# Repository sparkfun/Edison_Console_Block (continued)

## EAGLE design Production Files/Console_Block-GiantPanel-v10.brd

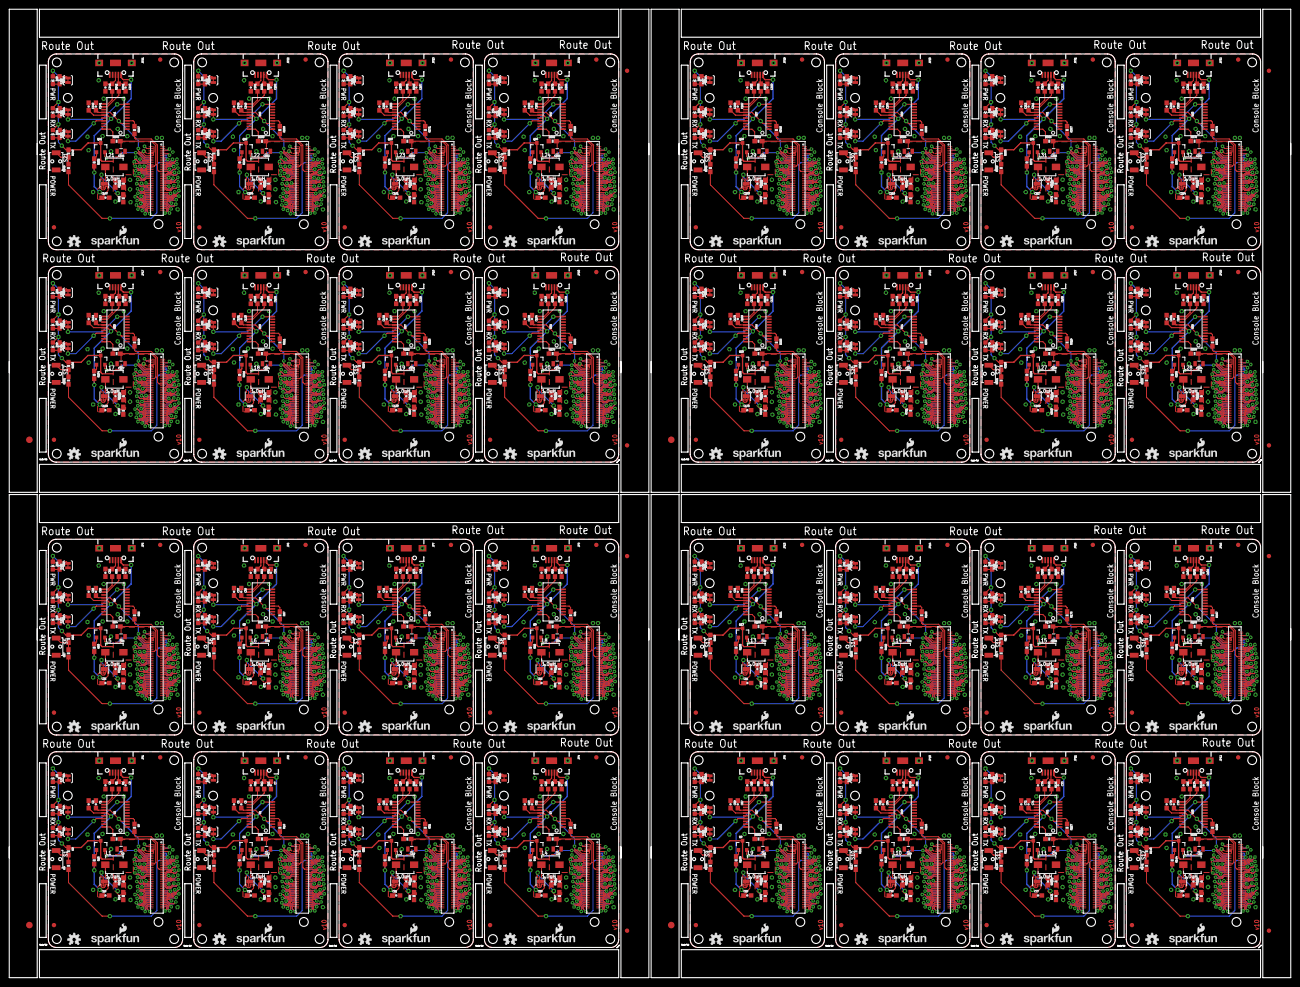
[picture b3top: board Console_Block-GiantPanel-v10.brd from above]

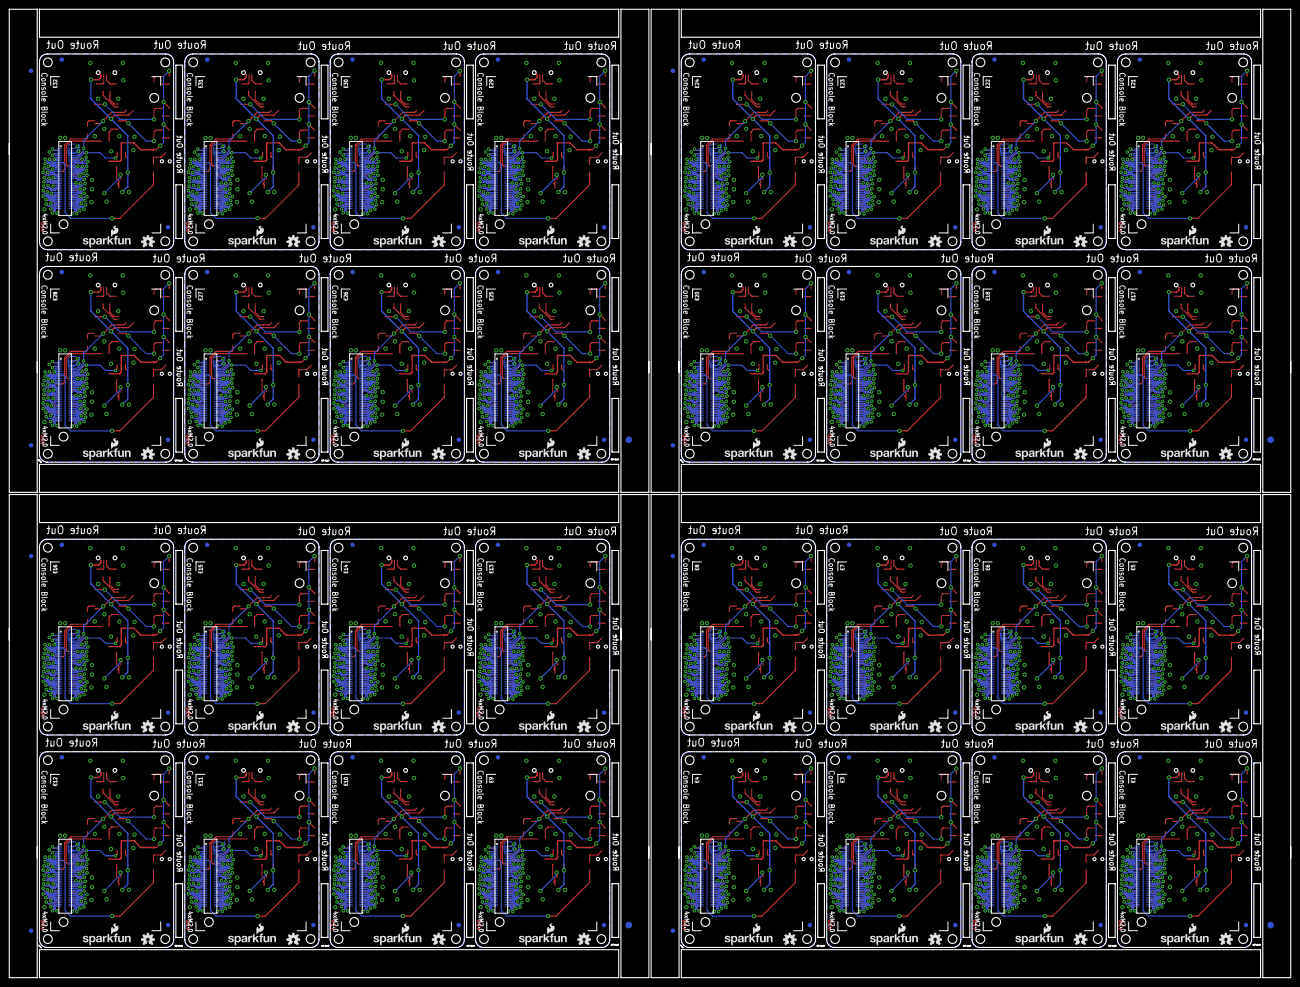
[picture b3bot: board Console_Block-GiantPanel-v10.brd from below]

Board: 2 copper layers, 291.1 x 220.0 mm, 1336 parts (204 on the bottom side), 2464 nets.

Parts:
C1, C2, C5, C6, C15, C16, C22, C23, C29, C30, C36, C37, C43, C44, C50, C51, C57, C58, C64, C65, C71, C72, C78, C79, C85, C86, C92, C93, C99, C100, C106, C107, C113, C114, C120, C121, C127, C128, C134, C135, C141, C142, C148, C149, C155, C156, C162, C163, C169, C170, C176, C177, C183, C184, C190, C191, C197, C198, C204, C205, C211, C212, C218, C219: 0.1uF; 0603-CAP
C3, C4, C7, C9, C11, C13, C17, C18, C20, C24, C25, C27, C31, C32, C34, C38, C39, C41, C45, C46, C48, C52, C53, C55, C59, C60, C62, C66, C67, C69, C73, C74, C76, C80, C81, C83, C87, C88, C90, C94, C95, C97, C101, C102, C104, C108, C109, C111, C115, C116, C118, C122, C123, C125, C129, C130, C132, C136, C137, C139, C143, C144, C146, C150, C151, C153, C157, C158, C160, C164, C165, C167, C171, C172, C174, C178, C179, C181, C185, C186, C188, C192, C193, C195, C199, C200, C202, C206, C207, C209, C213, C214, C216, C220, C221, C223: 47pF; 0603-CAP
C8, C12, C19, C26, C33, C40, C47, C54, C61, C68, C75, C82, C89, C96, C103, C110, C117, C124, C131, C138, C145, C152, C159, C166, C173, C180, C187, C194, C201, C208, C215, C222: 22uF; 0805
C10, C14, C21, C28, C35, C42, C49, C56, C63, C70, C77, C84, C91, C98, C105, C112, C119, C126, C133, C140, C147, C154, C161, C168, C175, C182, C189, C196, C203, C210, C217, C224: 4.7uF; 0603-CAP
D1, D4, D7, D10, D13, D16, D19, D22, D25, D28, D31, D34, D37, D40, D43, D46, D49, D52, D55, D58, D61, D64, D67, D70, D73, D76, D79, D82, D85, D88, D91, D94: RED; LED-0603
D2, D5, D8, D11, D14, D17, D20, D23, D26, D29, D32, D35, D38, D41, D44, D47, D50, D53, D56, D59, D62, D65, D68, D71, D74, D77, D80, D83, D86, D89, D92, D95: YELLOW; LED-0603
D3, D6, D9, D12, D15, D18, D21, D24, D27, D30, D33, D36, D39, D42, D45, D48, D51, D54, D57, D60, D63, D66, D69, D72, D75, D78, D81, D84, D87, D90, D93, D96: BLUE; LED-0603
E1, E2, E3, E4, E5, E6, E7, E8, E9, E10, E11, E12, E13, E14, E15, E16, E17, E18, E19, E20, E21, E22, E23, E24, E25, E26, E27, E28, E29, E30, E31, E32: EDISON_CONNECTOR_FULLMOUNTING_HOLES; EDISON_DAUGHTER
E$1, E$2, E$9, E$10, E$15, E$16, E$21, E$22: FIDUCIAL-1.5X3
E$3, E$4, E$5, E$6, E$7, E$8, E$11, E$12, E$13, E$14, E$17, E$18, E$19, E$20, E$23, E$24: FIDUCIAL-1X2
FID1, FID2, FID3, FID4, FID5, FID6, FID7, FID8, FID9, FID10, FID11, FID12, FID13, FID14, FID15, FID16, FID17, FID18, FID19, FID20, FID21, FID22, FID23, FID24, FID25, FID26, FID27, FID28, FID29, FID30, FID31, FID32, FID33, FID34, FID35, FID36, FID37, FID38, FID39, FID40, FID41, FID42, FID43, FID44, FID45, FID46, FID47, FID48, FID49, FID50, FID51, FID52, FID53, FID54, FID55, FID56, FID57, FID58, FID59, FID60, FID61, FID62, FID63, FID64, FID65, FID66, FID67, FID68, FID69, FID70, FID71, FID72, FID73, FID74, FID75, FID76, FID77, FID78, FID79, FID80, FID81, FID82, FID83, FID84, FID85, FID86, FID87, FID88, FID89, FID90, FID91, FID92, FID93, FID94, FID95, FID96, FID97, FID98, FID99, FID100, FID101, FID102, FID103, FID104, FID105, FID106, FID107, FID108, FID109, FID110, FID111, FID112, FID113, FID114, FID115, FID116, FID117, FID118, FID119, FID120, FID121, FID122, FID123, FID124, FID125, FID126, FID127, FID128: FIDUCIAL1X2; FIDUCIAL-1X2
JP1, JP2, JP3, JP4, JP5, JP6, JP7, JP8, JP9, JP10, JP11, JP12, JP13, JP14, JP15, JP16, JP17, JP18, JP19, JP20, JP21, JP22, JP23, JP24, JP25, JP26, JP27, JP28, JP29, JP30, JP31, JP32: USB_MICROB; USB-B-MICRO-SMD_V03
L1, L2, L3, L4, L5, L6, L7, L8, L9, L10, L11, L12, L13, L14, L15, L16, L17, L18, L19, L20, L21, L22, L23, L24, L25, L26, L27, L28, L29, L30, L31, L32: 1.0uH; INDUCTOR-SRP4020
LOGO1, LOGO3, LOGO6, LOGO7, LOGO10, LOGO11, LOGO14, LOGO15, LOGO18, LOGO19, LOGO22, LOGO23, LOGO26, LOGO27, LOGO30, LOGO31, LOGO34, LOGO35, LOGO38, LOGO39, LOGO42, LOGO43, LOGO46, LOGO47, LOGO50, LOGO51, LOGO54, LOGO55, LOGO58, LOGO59, LOGO62, LOGO63, LOGO66, LOGO67, LOGO70, LOGO71, LOGO74, LOGO75, LOGO78, LOGO79, LOGO82, LOGO83, LOGO86, LOGO87, LOGO90, LOGO91, LOGO94, LOGO95, LOGO98, LOGO99, LOGO102, LOGO103, LOGO106, LOGO107, LOGO110, LOGO111, LOGO114, LOGO115, LOGO118, LOGO119, LOGO122, LOGO123, LOGO126, LOGO127: SFE_LOGO_NAME_FLAME.1_INCH; SFE_LOGO_NAME_FLAME_.1
LOGO2, LOGO4, LOGO5, LOGO8, LOGO9, LOGO12, LOGO13, LOGO16, LOGO17, LOGO20, LOGO21, LOGO24, LOGO25, LOGO28, LOGO29, LOGO32, LOGO33, LOGO36, LOGO37, LOGO40, LOGO41, LOGO44, LOGO45, LOGO48, LOGO49, LOGO52, LOGO53, LOGO56, LOGO57, LOGO60, LOGO61, LOGO64, LOGO65, LOGO68, LOGO69, LOGO72, LOGO73, LOGO76, LOGO77, LOGO80, LOGO81, LOGO84, LOGO85, LOGO88, LOGO89, LOGO92, LOGO93, LOGO96, LOGO97, LOGO100, LOGO101, LOGO104, LOGO105, LOGO108, LOGO109, LOGO112, LOGO113, LOGO116, LOGO117, LOGO120, LOGO121, LOGO124, LOGO125, LOGO128: OSHW-LOGOS; OSHW-LOGO-S
Q1, Q2, Q3, Q4, Q5, Q6, Q7, Q8, Q9, Q10, Q11, Q12, Q13, Q14, Q15, Q16, Q17, Q18, Q19, Q20, Q21, Q22, Q23, Q24, Q25, Q26, Q27, Q28, Q29, Q30, Q31, Q32: BSS138; SOT23-3
R1, R2, R11, R12, R25, R26, R37, R38, R49, R50, R61, R62, R73, R74, R85, R86, R97, R98, R109, R110, R121, R122, R133, R134, R145, R146, R157, R158, R169, R170, R181, R182, R193, R194, R205, R206, R217, R218, R229, R230, R241, R242, R253, R254, R265, R266, R277, R278, R289, R290, R301, R302, R313, R314, R325, R326, R337, R338, R349, R350, R361, R362, R373, R374: 27; 0603
R3, R4, R5, R10, R15, R16, R17, R24, R27, R28, R29, R36, R39, R40, R41, R48, R51, R52, R53, R60, R63, R64, R65, R72, R75, R76, R77, R84, R87, R88, R89, R96, R99, R100, R101, R108, R111, R112, R113, R120, R123, R124, R125, R132, R135, R136, R137, R144, R147, R148, R149, R156, R159, R160, R161, R168, R171, R172, R173, R180, R183, R184, R185, R192, R195, R196, R197, R204, R207, R208, R209, R216, R219, R220, R221, R228, R231, R232, R233, R240, R243, R244, R245, R252, R255, R256, R257, R264, R267, R268, R269, R276, R279, R280, R281, R288, R291, R292, R293, R300, R303, R304, R305, R312, R315, R316, R317, R324, R327, R328, R329, R336, R339, R340, R341, R348, R351, R352, R353, R360, R363, R364, R365, R372, R375, R376, R377, R384: 1K; 0603-RES
R6, R7, R18, R19, R30, R31, R42, R43, R54, R55, R66, R67, R78, R79, R90, R91, R102, R103, R114, R115, R126, R127, R138, R139, R150, R151, R162, R163, R174, R175, R186, R187, R198, R199, R210, R211, R222, R223, R234, R235, R246, R247, R258, R259, R270, R271, R282, R283, R294, R295, R306, R307, R318, R319, R330, R331, R342, R343, R354, R355, R366, R367, R378, R379: 100; 0603-RES
R8, R20, R32, R44, R56, R68, R80, R92, R104, R116, R128, R140, R152, R164, R176, R188, R200, R212, R224, R236, R248, R260, R272, R284, R296, R308, R320, R332, R344, R356, R368, R380: 10K; 0603-RES
R9, R21, R33, R45, R57, R69, R81, R93, R105, R117, R129, R141, R153, R165, R177, R189, R201, R213, R225, R237, R249, R261, R273, R285, R297, R309, R321, R333, R345, R357, R369, R381: 22; 0603-RES
R13, R22, R34, R46, R58, R70, R82, R94, R106, R118, R130, R142, R154, R166, R178, R190, R202, R214, R226, R238, R250, R262, R274, R286, R298, R310, R322, R334, R346, R358, R370, R382: 680k; 0603-RES
R14, R23, R35, R47, R59, R71, R83, R95, R107, R119, R131, R143, R155, R167, R179, R191, R203, R215, R227, R239, R251, R263, R275, R287, R299, R311, R323, R335, R347, R359, R371, R383: 120k; 0603-RES
S1, S2, S3, S4, S5, S6, S7, S8, S9, S10, S11, S12, S13, S14, S15, S16, S17, S18, S19, S20, S21, S22, S23, S24, S25, S26, S27, S28, S29, S30, S31, S32: POWER; TACTILE_SWITCH-SMD-RIGHT-ANGLE
SJ1, SJ2, SJ3, SJ4, SJ5, SJ6, SJ7, SJ8, SJ9, SJ10, SJ11, SJ12, SJ13, SJ14, SJ15, SJ16, SJ17, SJ18, SJ19, SJ20, SJ21, SJ22, SJ23, SJ24, SJ25, SJ26, SJ27, SJ28, SJ29, SJ30, SJ31, SJ32, SJ33, SJ34, SJ35, SJ36, SJ37, SJ38, SJ39, SJ40, SJ41, SJ42, SJ43, SJ44, SJ45, SJ46, SJ47, SJ48, SJ49, SJ50, SJ51, SJ52, SJ53, SJ54, SJ55, SJ56, SJ57, SJ58, SJ59, SJ60, SJ61, SJ62, SJ63, SJ64, SJ65, SJ66, SJ67, SJ68, SJ69, SJ70, SJ71, SJ72, SJ73, SJ74, SJ75, SJ76, SJ77, SJ78, SJ79, SJ80, SJ81, SJ82, SJ83, SJ84, SJ85, SJ86, SJ87, SJ88, SJ89, SJ90, SJ91, SJ92, SJ93, SJ94, SJ95, SJ96: JUMPER-PAD-2-NC_BY_TRACE; PAD-JUMPER-2-NC_BY_TRACE_YES_SILK
U1, U2, U5, U7, U9, U11, U13, U15, U17, U19, U21, U23, U25, U27, U29, U31, U33, U35, U37, U39, U41, U43, U45, U47, U49, U51, U53, U55, U57, U59, U61, U63: FT231XS-U; SSOP20_L
U3, U4, U6, U8, U10, U12, U14, U16, U18, U20, U22, U24, U26, U28, U30, U32, U34, U36, U38, U40, U42, U44, U46, U48, U50, U52, U54, U56, U58, U60, U62, U64: TPS62065; WSON-8-PAD
U$1, U$2, U$3, U$4, U$5, U$6, U$7, U$8, U$9, U$10, U$11, U$12, U$13, U$14, U$15, U$16, U$17, U$18, U$19, U$20, U$21, U$22, U$23, U$24, U$25, U$26, U$27, U$28, U$29, U$30, U$31, U$32: EDISON_CONNECTOR_FULLHEADER; DF40C-70DP-0.4(51)

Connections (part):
1.8V: C1.2, E1.12, U2.3, U2.14, U$3.12
1.8V1: C5.2, E2.12, U1.3, U1.14, U$1.12
1.8V2: C15.2, E3.12, U5.3, U5.14, U$2.12
1.8V3: C22.2, E4.12, U7.3, U7.14, U$4.12
1.8V4: C29.2, E5.12, U9.3, U9.14, U$5.12
1.8V5: C36.2, E6.12, U11.3, U11.14, U$6.12
1.8V6: C43.2, E7.12, U13.3, U13.14, U$7.12
1.8V7: C50.2, E8.12, U15.3, U15.14, U$8.12
1.8V8: C57.2, E9.12, U17.3, U17.14, U$9.12
1.8V9: C64.2, E10.12, U19.3, U19.14, U$10.12
1.8V10: C71.2, E11.12, U21.3, U21.14, U$11.12
1.8V11: C78.2, E12.12, U23.3, U23.14, U$12.12
1.8V12: C85.2, E13.12, U25.3, U25.14, U$13.12
1.8V13: C92.2, E14.12, U27.3, U27.14, U$14.12
1.8V14: C99.2, E15.12, U29.3, U29.14, U$15.12
1.8V15: C106.2, E16.12, U31.3, U31.14, U$16.12
1.8V16: C113.2, E17.12, U33.3, U33.14, U$17.12
1.8V17: C120.2, E18.12, U35.3, U35.14, U$18.12
1.8V18: C127.2, E19.12, U37.3, U37.14, U$19.12
1.8V19: C134.2, E20.12, U39.3, U39.14, U$20.12
1.8V20: C141.2, E21.12, U41.3, U41.14, U$21.12
1.8V21: C148.2, E22.12, U43.3, U43.14, U$22.12
1.8V22: C155.2, E23.12, U45.3, U45.14, U$23.12
1.8V23: C162.2, E24.12, U47.3, U47.14, U$24.12
1.8V24: C169.2, E25.12, U49.3, U49.14, U$25.12
1.8V25: C176.2, E26.12, U51.3, U51.14, U$26.12
1.8V26: C183.2, E27.12, U53.3, U53.14, U$27.12
1.8V27: C190.2, E28.12, U55.3, U55.14, U$28.12
1.8V28: C197.2, E29.12, U57.3, U57.14, U$29.12
1.8V29: C204.2, E30.12, U59.3, U59.14, U$30.12
1.8V30: C211.2, E31.12, U61.3, U61.14, U$31.12
1.8V31: C218.2, E32.12, U63.3, U63.14, U$32.12
3.3V: E1.8, E1.10, U$3.8, U$3.10
3.3V1: E2.8, E2.10, U$1.8, U$1.10
3.3V2: E3.8, E3.10, U$2.8, U$2.10
3.3V3: E4.8, E4.10, U$4.8, U$4.10
3.3V4: E5.8, E5.10, U$5.8, U$5.10
3.3V5: E6.8, E6.10, U$6.8, U$6.10
3.3V6: E7.8, E7.10, U$7.8, U$7.10
3.3V7: E8.8, E8.10, U$8.8, U$8.10
3.3V8: E9.8, E9.10, U$9.8, U$9.10
3.3V9: E10.8, E10.10, U$10.8, U$10.10
3.3V10: E11.8, E11.10, U$11.8, U$11.10
3.3V11: E12.8, E12.10, U$12.8, U$12.10
3.3V12: E13.8, E13.10, U$13.8, U$13.10
3.3V13: E14.8, E14.10, U$14.8, U$14.10
3.3V14: E15.8, E15.10, U$15.8, U$15.10
3.3V15: E16.8, E16.10, U$16.8, U$16.10
3.3V16: E17.8, E17.10, U$17.8, U$17.10
3.3V17: E18.8, E18.10, U$18.8, U$18.10
3.3V18: E19.8, E19.10, U$19.8, U$19.10
3.3V19: E20.8, E20.10, U$20.8, U$20.10
3.3V20: E21.8, E21.10, U$21.8, U$21.10
3.3V21: E22.8, E22.10, U$22.8, U$22.10
3.3V22: E23.8, E23.10, U$23.8, U$23.10
3.3V23: E24.8, E24.10, U$24.8, U$24.10
3.3V24: E25.8, E25.10, U$25.8, U$25.10
3.3V25: E26.8, E26.10, U$26.8, U$26.10
3.3V26: E27.8, E27.10, U$27.8, U$27.10
3.3V27: E28.8, E28.10, U$28.8, U$28.10
3.3V28: E29.8, E29.10, U$29.8, U$29.10
3.3V29: E30.8, E30.10, U$30.8, U$30.10
3.3V30: E31.8, E31.10, U$31.8, U$31.10
3.3V31: E32.8, E32.10, U$32.8, U$32.10
5V: C2.2, C10.1, JP1.VBUS1, R10.2, U2.15, U4.5, U4.7, U4.8
5V1: C6.2, C14.1, JP2.VBUS1, R24.2, U1.15, U3.5, U3.7, U3.8
5V2: C16.2, C21.1, JP3.VBUS1, R36.2, U5.15, U6.5, U6.7, U6.8
5V3: C23.2, C28.1, JP4.VBUS1, R48.2, U7.15, U8.5, U8.7, U8.8
5V4: C30.2, C35.1, JP5.VBUS1, R60.2, U9.15, U10.5, U10.7, U10.8
5V5: C37.2, C42.1, JP6.VBUS1, R72.2, U11.15, U12.5, U12.7, U12.8
5V6: C44.2, C49.1, JP7.VBUS1, R84.2, U13.15, U14.5, U14.7, U14.8
5V7: C51.2, C56.1, JP8.VBUS1, R96.2, U15.15, U16.5, U16.7, U16.8
5V8: C58.2, C63.1, JP9.VBUS1, R108.2, U17.15, U18.5, U18.7, U18.8
5V9: C65.2, C70.1, JP10.VBUS1, R120.2, U19.15, U20.5, U20.7, U20.8
5V10: C72.2, C77.1, JP11.VBUS1, R132.2, U21.15, U22.5, U22.7, U22.8
5V11: C79.2, C84.1, JP12.VBUS1, R144.2, U23.15, U24.5, U24.7, U24.8
5V12: C86.2, C91.1, JP13.VBUS1, R156.2, U25.15, U26.5, U26.7, U26.8
5V13: C93.2, C98.1, JP14.VBUS1, R168.2, U27.15, U28.5, U28.7, U28.8
5V14: C100.2, C105.1, JP15.VBUS1, R180.2, U29.15, U30.5, U30.7, U30.8
5V15: C107.2, C112.1, JP16.VBUS1, R192.2, U31.15, U32.5, U32.7, U32.8
5V16: C114.2, C119.1, JP17.VBUS1, R204.2, U33.15, U34.5, U34.7, U34.8
5V17: C121.2, C126.1, JP18.VBUS1, R216.2, U35.15, U36.5, U36.7, U36.8
5V18: C128.2, C133.1, JP19.VBUS1, R228.2, U37.15, U38.5, U38.7, U38.8
5V19: C135.2, C140.1, JP20.VBUS1, R240.2, U39.15, U40.5, U40.7, U40.8
5V20: C142.2, C147.1, JP21.VBUS1, R252.2, U41.15, U42.5, U42.7, U42.8
5V21: C149.2, C154.1, JP22.VBUS1, R264.2, U43.15, U44.5, U44.7, U44.8
5V22: C156.2, C161.1, JP23.VBUS1, R276.2, U45.15, U46.5, U46.7, U46.8
5V23: C163.2, C168.1, JP24.VBUS1, R288.2, U47.15, U48.5, U48.7, U48.8
5V24: C170.2, C175.1, JP25.VBUS1, R300.2, U49.15, U50.5, U50.7, U50.8
5V25: C177.2, C182.1, JP26.VBUS1, R312.2, U51.15, U52.5, U52.7, U52.8
5V26: C184.2, C189.1, JP27.VBUS1, R324.2, U53.15, U54.5, U54.7, U54.8
5V27: C191.2, C196.1, JP28.VBUS1, R336.2, U55.15, U56.5, U56.7, U56.8
5V28: C198.2, C203.1, JP29.VBUS1, R348.2, U57.15, U58.5, U58.7, U58.8
5V29: C205.2, C210.1, JP30.VBUS1, R360.2, U59.15, U60.5, U60.7, U60.8
5V30: C212.2, C217.1, JP31.VBUS1, R372.2, U61.15, U62.5, U62.7, U62.8
5V31: C219.2, C224.1, JP32.VBUS1, R384.2, U63.15, U64.5, U64.7, U64.8
DCIN: E1.14, Q1.2, U$3.14
DCIN1: E2.14, Q2.2, U$1.14
DCIN2: E3.14, Q3.2, U$2.14
DCIN3: E4.14, Q4.2, U$4.14
DCIN4: E5.14, Q5.2, U$5.14
DCIN5: E6.14, Q6.2, U$6.14
DCIN6: E7.14, Q7.2, U$7.14
DCIN7: E8.14, Q8.2, U$8.14
DCIN8: E9.14, Q9.2, U$9.14
DCIN9: E10.14, Q10.2, U$10.14
DCIN10: E11.14, Q11.2, U$11.14
DCIN11: E12.14, Q12.2, U$12.14
DCIN12: E13.14, Q13.2, U$13.14
DCIN13: E14.14, Q14.2, U$14.14
DCIN14: E15.14, Q15.2, U$15.14
DCIN15: E16.14, Q16.2, U$16.14
DCIN16: E17.14, Q17.2, U$17.14
DCIN17: E18.14, Q18.2, U$18.14
DCIN18: E19.14, Q19.2, U$19.14
DCIN19: E20.14, Q20.2, U$20.14
DCIN20: E21.14, Q21.2, U$21.14
DCIN21: E22.14, Q22.2, U$22.14
DCIN22: E23.14, Q23.2, U$23.14
DCIN23: E24.14, Q24.2, U$24.14
DCIN24: E25.14, Q25.2, U$25.14
DCIN25: E26.14, Q26.2, U$26.14
DCIN26: E27.14, Q27.2, U$27.14
DCIN27: E28.14, Q28.2, U$28.14
DCIN28: E29.14, Q29.2, U$29.14
DCIN29: E30.14, Q30.2, U$30.14
DCIN30: E31.14, Q31.2, U$31.14
DCIN31: E32.14, Q32.2, U$32.14
FAULT: E1.19, U$3.19
FAULT1: E2.19, U$1.19
FAULT2: E3.19, U$2.19
FAULT3: E4.19, U$4.19
FAULT4: E5.19, U$5.19
FAULT5: E6.19, U$6.19
FAULT6: E7.19, U$7.19
FAULT7: E8.19, U$8.19
FAULT8: E9.19, U$9.19
FAULT9: E10.19, U$10.19
FAULT10: E11.19, U$11.19
FAULT11: E12.19, U$12.19
FAULT12: E13.19, U$13.19
FAULT13: E14.19, U$14.19
FAULT14: E15.19, U$15.19
FAULT15: E16.19, U$16.19
FAULT16: E17.19, U$17.19
FAULT17: E18.19, U$18.19
FAULT18: E19.19, U$19.19
FAULT19: E20.19, U$20.19
FAULT20: E21.19, U$21.19
FAULT21: E22.19, U$22.19
FAULT22: E23.19, U$23.19
FAULT23: E24.19, U$24.19
FAULT24: E25.19, U$25.19
FAULT25: E26.19, U$26.19
FAULT26: E27.19, U$27.19
FAULT27: E28.19, U$28.19
FAULT28: E29.19, U$29.19
FAULT29: E30.19, U$30.19
FAULT30: E31.19, U$31.19
FAULT31: E32.19, U$32.19
FW_RCVR: E1.69, U$3.69
FW_RCVR1: E2.69, U$1.69
FW_RCVR2: E3.69, U$2.69
FW_RCVR3: E4.69, U$4.69
FW_RCVR4: E5.69, U$5.69
FW_RCVR5: E6.69, U$6.69
FW_RCVR6: E7.69, U$7.69
FW_RCVR7: E8.69, U$8.69
FW_RCVR8: E9.69, U$9.69
FW_RCVR9: E10.69, U$10.69
FW_RCVR10: E11.69, U$11.69
FW_RCVR11: E12.69, U$12.69
FW_RCVR12: E13.69, U$13.69
FW_RCVR13: E14.69, U$14.69
FW_RCVR14: E15.69, U$15.69
FW_RCVR15: E16.69, U$16.69
FW_RCVR16: E17.69, U$17.69
FW_RCVR17: E18.69, U$18.69
FW_RCVR18: E19.69, U$19.69
FW_RCVR19: E20.69, U$20.69
FW_RCVR20: E21.69, U$21.69
FW_RCVR21: E22.69, U$22.69
FW_RCVR22: E23.69, U$23.69
FW_RCVR23: E24.69, U$24.69
FW_RCVR24: E25.69, U$25.69
FW_RCVR25: E26.69, U$26.69
FW_RCVR26: E27.69, U$27.69
FW_RCVR27: E28.69, U$28.69
FW_RCVR28: E29.69, U$29.69
FW_RCVR29: E30.69, U$30.69
FW_RCVR30: E31.69, U$31.69
FW_RCVR31: E32.69, U$32.69
GND: C1.1, C2.1, C3.2, C4.2, C8.2, C10.2, E1.1, E1.5, E1.9, E1.11, E1.13, E1.15, JP1.GND1, JP1.SHIELD1, JP1.SHIELD2, JP1.SHIELD3, R14.1, S1.2, SJ3.1, U2.6, U2.16, U4.1, U4.3, U4.6, U4.PAD, U$3.1, U$3.5, U$3.9, U$3.11, U$3.13, U$3.15
GND1: C5.1, C6.1, C7.2, C11.2, C12.2, C14.2, E2.1, E2.5, E2.9, E2.11, E2.13, E2.15, JP2.GND1, JP2.SHIELD1, JP2.SHIELD2, JP2.SHIELD3, R23.1, S2.2, SJ6.1, U1.6, U1.16, U3.1, U3.3, U3.6, U3.PAD, U$1.1, U$1.5, U$1.9, U$1.11, U$1.13, U$1.15
GND2: C15.1, C16.1, C17.2, C18.2, C19.2, C21.2, E3.1, E3.5, E3.9, E3.11, E3.13, E3.15, JP3.GND1, JP3.SHIELD1, JP3.SHIELD2, JP3.SHIELD3, R35.1, S3.2, SJ9.1, U5.6, U5.16, U6.1, U6.3, U6.6, U6.PAD, U$2.1, U$2.5, U$2.9, U$2.11, U$2.13, U$2.15
GND3: C22.1, C23.1, C24.2, C25.2, C26.2, C28.2, E4.1, E4.5, E4.9, E4.11, E4.13, E4.15, JP4.GND1, JP4.SHIELD1, JP4.SHIELD2, JP4.SHIELD3, R47.1, S4.2, SJ12.1, U7.6, U7.16, U8.1, U8.3, U8.6, U8.PAD, U$4.1, U$4.5, U$4.9, U$4.11, U$4.13, U$4.15
GND4: C29.1, C30.1, C31.2, C32.2, C33.2, C35.2, E5.1, E5.5, E5.9, E5.11, E5.13, E5.15, JP5.GND1, JP5.SHIELD1, JP5.SHIELD2, JP5.SHIELD3, R59.1, S5.2, SJ15.1, U9.6, U9.16, U10.1, U10.3, U10.6, U10.PAD, U$5.1, U$5.5, U$5.9, U$5.11, U$5.13, U$5.15
GND5: C36.1, C37.1, C38.2, C39.2, C40.2, C42.2, E6.1, E6.5, E6.9, E6.11, E6.13, E6.15, JP6.GND1, JP6.SHIELD1, JP6.SHIELD2, JP6.SHIELD3, R71.1, S6.2, SJ18.1, U11.6, U11.16, U12.1, U12.3, U12.6, U12.PAD, U$6.1, U$6.5, U$6.9, U$6.11, U$6.13, U$6.15
GND6: C43.1, C44.1, C45.2, C46.2, C47.2, C49.2, E7.1, E7.5, E7.9, E7.11, E7.13, E7.15, JP7.GND1, JP7.SHIELD1, JP7.SHIELD2, JP7.SHIELD3, R83.1, S7.2, SJ21.1, U13.6, U13.16, U14.1, U14.3, U14.6, U14.PAD, U$7.1, U$7.5, U$7.9, U$7.11, U$7.13, U$7.15
GND7: C50.1, C51.1, C52.2, C53.2, C54.2, C56.2, E8.1, E8.5, E8.9, E8.11, E8.13, E8.15, JP8.GND1, JP8.SHIELD1, JP8.SHIELD2, JP8.SHIELD3, R95.1, S8.2, SJ24.1, U15.6, U15.16, U16.1, U16.3, U16.6, U16.PAD, U$8.1, U$8.5, U$8.9, U$8.11, U$8.13, U$8.15
GND8: C57.1, C58.1, C59.2, C60.2, C61.2, C63.2, E9.1, E9.5, E9.9, E9.11, E9.13, E9.15, JP9.GND1, JP9.SHIELD1, JP9.SHIELD2, JP9.SHIELD3, R107.1, S9.2, SJ27.1, U17.6, U17.16, U18.1, U18.3, U18.6, U18.PAD, U$9.1, U$9.5, U$9.9, U$9.11, U$9.13, U$9.15
GND9: C64.1, C65.1, C66.2, C67.2, C68.2, C70.2, E10.1, E10.5, E10.9, E10.11, E10.13, E10.15, JP10.GND1, JP10.SHIELD1, JP10.SHIELD2, JP10.SHIELD3, R119.1, S10.2, SJ30.1, U19.6, U19.16, U20.1, U20.3, U20.6, U20.PAD, U$10.1, U$10.5, U$10.9, U$10.11, U$10.13, U$10.15
GND10: C71.1, C72.1, C73.2, C74.2, C75.2, C77.2, E11.1, E11.5, E11.9, E11.11, E11.13, E11.15, JP11.GND1, JP11.SHIELD1, JP11.SHIELD2, JP11.SHIELD3, R131.1, S11.2, SJ33.1, U21.6, U21.16, U22.1, U22.3, U22.6, U22.PAD, U$11.1, U$11.5, U$11.9, U$11.11, U$11.13, U$11.15
GND11: C78.1, C79.1, C80.2, C81.2, C82.2, C84.2, E12.1, E12.5, E12.9, E12.11, E12.13, E12.15, JP12.GND1, JP12.SHIELD1, JP12.SHIELD2, JP12.SHIELD3, R143.1, S12.2, SJ36.1, U23.6, U23.16, U24.1, U24.3, U24.6, U24.PAD, U$12.1, U$12.5, U$12.9, U$12.11, U$12.13, U$12.15
GND12: C85.1, C86.1, C87.2, C88.2, C89.2, C91.2, E13.1, E13.5, E13.9, E13.11, E13.13, E13.15, JP13.GND1, JP13.SHIELD1, JP13.SHIELD2, JP13.SHIELD3, R155.1, S13.2, SJ39.1, U25.6, U25.16, U26.1, U26.3, U26.6, U26.PAD, U$13.1, U$13.5, U$13.9, U$13.11, U$13.13, U$13.15
GND13: C92.1, C93.1, C94.2, C95.2, C96.2, C98.2, E14.1, E14.5, E14.9, E14.11, E14.13, E14.15, JP14.GND1, JP14.SHIELD1, JP14.SHIELD2, JP14.SHIELD3, R167.1, S14.2, SJ42.1, U27.6, U27.16, U28.1, U28.3, U28.6, U28.PAD, U$14.1, U$14.5, U$14.9, U$14.11, U$14.13, U$14.15
GND14: C99.1, C100.1, C101.2, C102.2, C103.2, C105.2, E15.1, E15.5, E15.9, E15.11, E15.13, E15.15, JP15.GND1, JP15.SHIELD1, JP15.SHIELD2, JP15.SHIELD3, R179.1, S15.2, SJ45.1, U29.6, U29.16, U30.1, U30.3, U30.6, U30.PAD, U$15.1, U$15.5, U$15.9, U$15.11, U$15.13, U$15.15
GND15: C106.1, C107.1, C108.2, C109.2, C110.2, C112.2, E16.1, E16.5, E16.9, E16.11, E16.13, E16.15, JP16.GND1, JP16.SHIELD1, JP16.SHIELD2, JP16.SHIELD3, R191.1, S16.2, SJ48.1, U31.6, U31.16, U32.1, U32.3, U32.6, U32.PAD, U$16.1, U$16.5, U$16.9, U$16.11, U$16.13, U$16.15
GND16: C113.1, C114.1, C115.2, C116.2, C117.2, C119.2, E17.1, E17.5, E17.9, E17.11, E17.13, E17.15, JP17.GND1, JP17.SHIELD1, JP17.SHIELD2, JP17.SHIELD3, R203.1, S17.2, SJ51.1, U33.6, U33.16, U34.1, U34.3, U34.6, U34.PAD, U$17.1, U$17.5, U$17.9, U$17.11, U$17.13, U$17.15
GND17: C120.1, C121.1, C122.2, C123.2, C124.2, C126.2, E18.1, E18.5, E18.9, E18.11, E18.13, E18.15, JP18.GND1, JP18.SHIELD1, JP18.SHIELD2, JP18.SHIELD3, R215.1, S18.2, SJ54.1, U35.6, U35.16, U36.1, U36.3, U36.6, U36.PAD, U$18.1, U$18.5, U$18.9, U$18.11, U$18.13, U$18.15
GND18: C127.1, C128.1, C129.2, C130.2, C131.2, C133.2, E19.1, E19.5, E19.9, E19.11, E19.13, E19.15, JP19.GND1, JP19.SHIELD1, JP19.SHIELD2, JP19.SHIELD3, R227.1, S19.2, SJ57.1, U37.6, U37.16, U38.1, U38.3, U38.6, U38.PAD, U$19.1, U$19.5, U$19.9, U$19.11, U$19.13, U$19.15
GND19: C134.1, C135.1, C136.2, C137.2, C138.2, C140.2, E20.1, E20.5, E20.9, E20.11, E20.13, E20.15, JP20.GND1, JP20.SHIELD1, JP20.SHIELD2, JP20.SHIELD3, R239.1, S20.2, SJ60.1, U39.6, U39.16, U40.1, U40.3, U40.6, U40.PAD, U$20.1, U$20.5, U$20.9, U$20.11, U$20.13, U$20.15
GND20: C141.1, C142.1, C143.2, C144.2, C145.2, C147.2, E21.1, E21.5, E21.9, E21.11, E21.13, E21.15, JP21.GND1, JP21.SHIELD1, JP21.SHIELD2, JP21.SHIELD3, R251.1, S21.2, SJ63.1, U41.6, U41.16, U42.1, U42.3, U42.6, U42.PAD, U$21.1, U$21.5, U$21.9, U$21.11, U$21.13, U$21.15
GND21: C148.1, C149.1, C150.2, C151.2, C152.2, C154.2, E22.1, E22.5, E22.9, E22.11, E22.13, E22.15, JP22.GND1, JP22.SHIELD1, JP22.SHIELD2, JP22.SHIELD3, R263.1, S22.2, SJ66.1, U43.6, U43.16, U44.1, U44.3, U44.6, U44.PAD, U$22.1, U$22.5, U$22.9, U$22.11, U$22.13, U$22.15
GND22: C155.1, C156.1, C157.2, C158.2, C159.2, C161.2, E23.1, E23.5, E23.9, E23.11, E23.13, E23.15, JP23.GND1, JP23.SHIELD1, JP23.SHIELD2, JP23.SHIELD3, R275.1, S23.2, SJ69.1, U45.6, U45.16, U46.1, U46.3, U46.6, U46.PAD, U$23.1, U$23.5, U$23.9, U$23.11, U$23.13, U$23.15
GND23: C162.1, C163.1, C164.2, C165.2, C166.2, C168.2, E24.1, E24.5, E24.9, E24.11, E24.13, E24.15, JP24.GND1, JP24.SHIELD1, JP24.SHIELD2, JP24.SHIELD3, R287.1, S24.2, SJ72.1, U47.6, U47.16, U48.1, U48.3, U48.6, U48.PAD, U$24.1, U$24.5, U$24.9, U$24.11, U$24.13, U$24.15
GND24: C169.1, C170.1, C171.2, C172.2, C173.2, C175.2, E25.1, E25.5, E25.9, E25.11, E25.13, E25.15, JP25.GND1, JP25.SHIELD1, JP25.SHIELD2, JP25.SHIELD3, R299.1, S25.2, SJ75.1, U49.6, U49.16, U50.1, U50.3, U50.6, U50.PAD, U$25.1, U$25.5, U$25.9, U$25.11, U$25.13, U$25.15
GND25: C176.1, C177.1, C178.2, C179.2, C180.2, C182.2, E26.1, E26.5, E26.9, E26.11, E26.13, E26.15, JP26.GND1, JP26.SHIELD1, JP26.SHIELD2, JP26.SHIELD3, R311.1, S26.2, SJ78.1, U51.6, U51.16, U52.1, U52.3, U52.6, U52.PAD, U$26.1, U$26.5, U$26.9, U$26.11, U$26.13, U$26.15
GND26: C183.1, C184.1, C185.2, C186.2, C187.2, C189.2, E27.1, E27.5, E27.9, E27.11, E27.13, E27.15, JP27.GND1, JP27.SHIELD1, JP27.SHIELD2, JP27.SHIELD3, R323.1, S27.2, SJ81.1, U53.6, U53.16, U54.1, U54.3, U54.6, U54.PAD, U$27.1, U$27.5, U$27.9, U$27.11, U$27.13, U$27.15
GND27: C190.1, C191.1, C192.2, C193.2, C194.2, C196.2, E28.1, E28.5, E28.9, E28.11, E28.13, E28.15, JP28.GND1, JP28.SHIELD1, JP28.SHIELD2, JP28.SHIELD3, R335.1, S28.2, SJ84.1, U55.6, U55.16, U56.1, U56.3, U56.6, U56.PAD, U$28.1, U$28.5, U$28.9, U$28.11, U$28.13, U$28.15
GND28: C197.1, C198.1, C199.2, C200.2, C201.2, C203.2, E29.1, E29.5, E29.9, E29.11, E29.13, E29.15, JP29.GND1, JP29.SHIELD1, JP29.SHIELD2, JP29.SHIELD3, R347.1, S29.2, SJ87.1, U57.6, U57.16, U58.1, U58.3, U58.6, U58.PAD, U$29.1, U$29.5, U$29.9, U$29.11, U$29.13, U$29.15
GND29: C204.1, C205.1, C206.2, C207.2, C208.2, C210.2, E30.1, E30.5, E30.9, E30.11, E30.13, E30.15, JP30.GND1, JP30.SHIELD1, JP30.SHIELD2, JP30.SHIELD3, R359.1, S30.2, SJ90.1, U59.6, U59.16, U60.1, U60.3, U60.6, U60.PAD, U$30.1, U$30.5, U$30.9, U$30.11, U$30.13, U$30.15
GND30: C211.1, C212.1, C213.2, C214.2, C215.2, C217.2, E31.1, E31.5, E31.9, E31.11, E31.13, E31.15, JP31.GND1, JP31.SHIELD1, JP31.SHIELD2, JP31.SHIELD3, R371.1, S31.2, SJ93.1, U61.6, U61.16, U62.1, U62.3, U62.6, U62.PAD, U$31.1, U$31.5, U$31.9, U$31.11, U$31.13, U$31.15
GND31: C218.1, C219.1, C220.2, C221.2, C222.2, C224.2, E32.1, E32.5, E32.9, E32.11, E32.13, E32.15, JP32.GND1, JP32.SHIELD1, JP32.SHIELD2, JP32.SHIELD3, R383.1, S32.2, SJ96.1, U63.6, U63.16, U64.1, U64.3, U64.6, U64.PAD, U$32.1, U$32.5, U$32.9, U$32.11, U$32.13, U$32.15
GP1: E2.48, U$1.48
GP2: E2.42, U$1.42
GP3: E2.34, U$1.34
GP4: E2.32, U$1.32
GP5: E2.30, U$1.30
GP6: E2.28, U$1.28
GP7: E2.26, U$1.26
GP8: E2.25, U$1.25
GP9: E2.24, U$1.24
GP10: E3.48, U$2.48
GP11: E3.42, U$2.42
GP12: E3.34, U$2.34
GP12_PWM0: E1.35, U$3.35
GP12_PWM1: E2.35, U$1.35
GP12_PWM2: E3.35, U$2.35
GP12_PWM3: E4.35, U$4.35
GP12_PWM4: E5.35, U$5.35
GP12_PWM5: E6.35, U$6.35
GP12_PWM6: E7.35, U$7.35
GP12_PWM7: E8.35, U$8.35
GP12_PWM8: E9.35, U$9.35
GP12_PWM9: E10.35, U$10.35
GP12_PWM10: E11.35, U$11.35
GP12_PWM11: E12.35, U$12.35
GP12_PWM12: E13.35, U$13.35
GP12_PWM13: E14.35, U$14.35
GP12_PWM14: E15.35, U$15.35
GP12_PWM15: E16.35, U$16.35
GP12_PWM16: E17.35, U$17.35
GP12_PWM17: E18.35, U$18.35
GP12_PWM18: E19.35, U$19.35
GP12_PWM19: E20.35, U$20.35
GP12_PWM20: E21.35, U$21.35
GP12_PWM21: E22.35, U$22.35
GP12_PWM22: E23.35, U$23.35
GP12_PWM23: E24.35, U$24.35
GP12_PWM24: E25.35, U$25.35
GP12_PWM25: E26.35, U$26.35
GP12_PWM26: E27.35, U$27.35
GP12_PWM27: E28.35, U$28.35
GP12_PWM28: E29.35, U$29.35
GP12_PWM29: E30.35, U$30.35
GP12_PWM30: E31.35, U$31.35
GP12_PWM31: E32.35, U$32.35
GP13: E3.32, U$2.32
GP13_PWM1: E1.33, U$3.33
GP13_PWM2: E2.33, U$1.33
GP13_PWM3: E3.33, U$2.33
GP13_PWM4: E4.33, U$4.33
GP13_PWM5: E5.33, U$5.33
GP13_PWM6: E6.33, U$6.33
GP13_PWM7: E7.33, U$7.33
GP13_PWM8: E8.33, U$8.33
GP13_PWM9: E9.33, U$9.33
GP13_PWM10: E10.33, U$10.33
GP13_PWM11: E11.33, U$11.33
GP13_PWM12: E12.33, U$12.33
GP13_PWM13: E13.33, U$13.33
GP13_PWM14: E14.33, U$14.33
GP13_PWM15: E15.33, U$15.33
GP13_PWM16: E16.33, U$16.33
GP13_PWM17: E17.33, U$17.33
GP13_PWM18: E18.33, U$18.33
GP13_PWM19: E19.33, U$19.33
GP13_PWM20: E20.33, U$20.33
GP13_PWM21: E21.33, U$21.33
GP13_PWM22: E22.33, U$22.33
GP13_PWM23: E23.33, U$23.33
GP13_PWM24: E24.33, U$24.33
GP13_PWM25: E25.33, U$25.33
GP13_PWM26: E26.33, U$26.33
GP13_PWM27: E27.33, U$27.33
GP13_PWM28: E28.33, U$28.33
GP13_PWM29: E29.33, U$29.33
GP13_PWM30: E30.33, U$30.33
GP13_PWM31: E31.33, U$31.33
GP13_PWM32: E32.33, U$32.33
GP14: E1.48, U$3.48
GP15: E1.42, U$3.42
GP16: E3.30, U$2.30
GP17: E3.28, U$2.28
GP18: E3.26, U$2.26
GP19: E3.25, U$2.25
GP19_I2C_1_SCL: E1.41, U$3.41
GP19_I2C_1_SCL1: E2.41, U$1.41
GP19_I2C_1_SCL2: E3.41, U$2.41
GP19_I2C_1_SCL3: E4.41, U$4.41
GP19_I2C_1_SCL4: E5.41, U$5.41
GP19_I2C_1_SCL5: E6.41, U$6.41
GP19_I2C_1_SCL6: E7.41, U$7.41
GP19_I2C_1_SCL7: E8.41, U$8.41
GP19_I2C_1_SCL8: E9.41, U$9.41
GP19_I2C_1_SCL9: E10.41, U$10.41
GP19_I2C_1_SCL10: E11.41, U$11.41
GP19_I2C_1_SCL11: E12.41, U$12.41
GP19_I2C_1_SCL12: E13.41, U$13.41
GP19_I2C_1_SCL13: E14.41, U$14.41
GP19_I2C_1_SCL14: E15.41, U$15.41
GP19_I2C_1_SCL15: E16.41, U$16.41
GP19_I2C_1_SCL16: E17.41, U$17.41
GP19_I2C_1_SCL17: E18.41, U$18.41
GP19_I2C_1_SCL18: E19.41, U$19.41
GP19_I2C_1_SCL19: E20.41, U$20.41
GP19_I2C_1_SCL20: E21.41, U$21.41
GP19_I2C_1_SCL21: E22.41, U$22.41
GP19_I2C_1_SCL22: E23.41, U$23.41
GP19_I2C_1_SCL23: E24.41, U$24.41
GP19_I2C_1_SCL24: E25.41, U$25.41
GP19_I2C_1_SCL25: E26.41, U$26.41
GP19_I2C_1_SCL26: E27.41, U$27.41
GP19_I2C_1_SCL27: E28.41, U$28.41
GP19_I2C_1_SCL28: E29.41, U$29.41
GP19_I2C_1_SCL29: E30.41, U$30.41
GP19_I2C_1_SCL30: E31.41, U$31.41
GP19_I2C_1_SCL31: E32.41, U$32.41
GP20: E3.24, U$2.24
GP20_I2C_1_SDA: E1.43, U$3.43
GP20_I2C_1_SDA1: E2.43, U$1.43
GP20_I2C_1_SDA2: E3.43, U$2.43
GP20_I2C_1_SDA3: E4.43, U$4.43
GP20_I2C_1_SDA4: E5.43, U$5.43
GP20_I2C_1_SDA5: E6.43, U$6.43
GP20_I2C_1_SDA6: E7.43, U$7.43
GP20_I2C_1_SDA7: E8.43, U$8.43
GP20_I2C_1_SDA8: E9.43, U$9.43
GP20_I2C_1_SDA9: E10.43, U$10.43
GP20_I2C_1_SDA10: E11.43, U$11.43
GP20_I2C_1_SDA11: E12.43, U$12.43
GP20_I2C_1_SDA12: E13.43, U$13.43
GP20_I2C_1_SDA13: E14.43, U$14.43
GP20_I2C_1_SDA14: E15.43, U$15.43
GP20_I2C_1_SDA15: E16.43, U$16.43
GP20_I2C_1_SDA16: E17.43, U$17.43
GP20_I2C_1_SDA17: E18.43, U$18.43
GP20_I2C_1_SDA18: E19.43, U$19.43
GP20_I2C_1_SDA19: E20.43, U$20.43
GP20_I2C_1_SDA20: E21.43, U$21.43
GP20_I2C_1_SDA21: E22.43, U$22.43
GP20_I2C_1_SDA22: E23.43, U$23.43
GP20_I2C_1_SDA23: E24.43, U$24.43
GP20_I2C_1_SDA24: E25.43, U$25.43
GP20_I2C_1_SDA25: E26.43, U$26.43
GP20_I2C_1_SDA26: E27.43, U$27.43
GP20_I2C_1_SDA27: E28.43, U$28.43
GP20_I2C_1_SDA28: E29.43, U$29.43
GP20_I2C_1_SDA29: E30.43, U$30.43
GP20_I2C_1_SDA30: E31.43, U$31.43
GP20_I2C_1_SDA31: E32.43, U$32.43
GP21: E4.48, U$4.48
GP22: E4.42, U$4.42
GP23: E4.34, U$4.34
GP24: E4.32, U$4.32
GP25: E4.30, U$4.30
GP26: E4.28, U$4.28
GP27: E4.26, U$4.26
GP27_I2C_6_SCL: E1.45, U$3.45
GP27_I2C_6_SCL1: E2.45, U$1.45
GP27_I2C_6_SCL2: E3.45, U$2.45
GP27_I2C_6_SCL3: E4.45, U$4.45
GP27_I2C_6_SCL4: E5.45, U$5.45
GP27_I2C_6_SCL5: E6.45, U$6.45
GP27_I2C_6_SCL6: E7.45, U$7.45
GP27_I2C_6_SCL7: E8.45, U$8.45
GP27_I2C_6_SCL8: E9.45, U$9.45
GP27_I2C_6_SCL9: E10.45, U$10.45
GP27_I2C_6_SCL10: E11.45, U$11.45
GP27_I2C_6_SCL11: E12.45, U$12.45
GP27_I2C_6_SCL12: E13.45, U$13.45
GP27_I2C_6_SCL13: E14.45, U$14.45
GP27_I2C_6_SCL14: E15.45, U$15.45
GP27_I2C_6_SCL15: E16.45, U$16.45
GP27_I2C_6_SCL16: E17.45, U$17.45
GP27_I2C_6_SCL17: E18.45, U$18.45
GP27_I2C_6_SCL18: E19.45, U$19.45
GP27_I2C_6_SCL19: E20.45, U$20.45
GP27_I2C_6_SCL20: E21.45, U$21.45
GP27_I2C_6_SCL21: E22.45, U$22.45
GP27_I2C_6_SCL22: E23.45, U$23.45
GP27_I2C_6_SCL23: E24.45, U$24.45
GP27_I2C_6_SCL24: E25.45, U$25.45
GP27_I2C_6_SCL25: E26.45, U$26.45
GP27_I2C_6_SCL26: E27.45, U$27.45
GP27_I2C_6_SCL27: E28.45, U$28.45
GP27_I2C_6_SCL28: E29.45, U$29.45
GP27_I2C_6_SCL29: E30.45, U$30.45
GP27_I2C_6_SCL30: E31.45, U$31.45
GP27_I2C_6_SCL31: E32.45, U$32.45
GP28: E4.25, U$4.25
GP28_I2C_6_SDA: E1.47, U$3.47
GP28_I2C_6_SDA1: E2.47, U$1.47
GP28_I2C_6_SDA2: E3.47, U$2.47
GP28_I2C_6_SDA3: E4.47, U$4.47
GP28_I2C_6_SDA4: E5.47, U$5.47
GP28_I2C_6_SDA5: E6.47, U$6.47
GP28_I2C_6_SDA6: E7.47, U$7.47
GP28_I2C_6_SDA7: E8.47, U$8.47
GP28_I2C_6_SDA8: E9.47, U$9.47
GP28_I2C_6_SDA9: E10.47, U$10.47
GP28_I2C_6_SDA10: E11.47, U$11.47
GP28_I2C_6_SDA11: E12.47, U$12.47
GP28_I2C_6_SDA12: E13.47, U$13.47
GP28_I2C_6_SDA13: E14.47, U$14.47
GP28_I2C_6_SDA14: E15.47, U$15.47
GP28_I2C_6_SDA15: E16.47, U$16.47
GP28_I2C_6_SDA16: E17.47, U$17.47
GP28_I2C_6_SDA17: E18.47, U$18.47
GP28_I2C_6_SDA18: E19.47, U$19.47
GP28_I2C_6_SDA19: E20.47, U$20.47
GP28_I2C_6_SDA20: E21.47, U$21.47
GP28_I2C_6_SDA21: E22.47, U$22.47
GP28_I2C_6_SDA22: E23.47, U$23.47
GP28_I2C_6_SDA23: E24.47, U$24.47
GP28_I2C_6_SDA24: E25.47, U$25.47
GP28_I2C_6_SDA25: E26.47, U$26.47
GP28_I2C_6_SDA26: E27.47, U$27.47
GP28_I2C_6_SDA27: E28.47, U$28.47
GP28_I2C_6_SDA28: E29.47, U$29.47
GP28_I2C_6_SDA29: E30.47, U$30.47
GP28_I2C_6_SDA30: E31.47, U$31.47
GP28_I2C_6_SDA31: E32.47, U$32.47
GP29: E4.24, U$4.24
GP30: E5.48, U$5.48
GP31: E5.42, U$5.42
GP32: E5.34, U$5.34
GP33: E5.32, U$5.32
GP34: E5.30, U$5.30
GP35: E5.28, U$5.28
GP36: E5.26, U$5.26
GP37: E5.25, U$5.25
GP38: E5.24, U$5.24
GP39: E6.48, U$6.48
GP40: E6.42, U$6.42
GP40_I2S_2_CLK: E1.52, U$3.52
GP40_I2S_2_CLK1: E2.52, U$1.52
GP40_I2S_2_CLK2: E3.52, U$2.52
GP40_I2S_2_CLK3: E4.52, U$4.52
GP40_I2S_2_CLK4: E5.52, U$5.52
GP40_I2S_2_CLK5: E6.52, U$6.52
GP40_I2S_2_CLK6: E7.52, U$7.52
GP40_I2S_2_CLK7: E8.52, U$8.52
GP40_I2S_2_CLK8: E9.52, U$9.52
GP40_I2S_2_CLK9: E10.52, U$10.52
GP40_I2S_2_CLK10: E11.52, U$11.52
GP40_I2S_2_CLK11: E12.52, U$12.52
GP40_I2S_2_CLK12: E13.52, U$13.52
GP40_I2S_2_CLK13: E14.52, U$14.52
GP40_I2S_2_CLK14: E15.52, U$15.52
GP40_I2S_2_CLK15: E16.52, U$16.52
GP40_I2S_2_CLK16: E17.52, U$17.52
GP40_I2S_2_CLK17: E18.52, U$18.52
GP40_I2S_2_CLK18: E19.52, U$19.52
GP40_I2S_2_CLK19: E20.52, U$20.52
GP40_I2S_2_CLK20: E21.52, U$21.52
GP40_I2S_2_CLK21: E22.52, U$22.52
GP40_I2S_2_CLK22: E23.52, U$23.52
GP40_I2S_2_CLK23: E24.52, U$24.52
GP40_I2S_2_CLK24: E25.52, U$25.52
GP40_I2S_2_CLK25: E26.52, U$26.52
GP40_I2S_2_CLK26: E27.52, U$27.52
GP40_I2S_2_CLK27: E28.52, U$28.52
GP40_I2S_2_CLK28: E29.52, U$29.52
GP40_I2S_2_CLK29: E30.52, U$30.52
GP40_I2S_2_CLK30: E31.52, U$31.52
GP40_I2S_2_CLK31: E32.52, U$32.52
GP41: E6.34, U$6.34
GP41_I2S_2_FS: E1.54, U$3.54
GP41_I2S_2_FS1: E2.54, U$1.54
GP41_I2S_2_FS2: E3.54, U$2.54
GP41_I2S_2_FS3: E4.54, U$4.54
GP41_I2S_2_FS4: E5.54, U$5.54
GP41_I2S_2_FS5: E6.54, U$6.54
GP41_I2S_2_FS6: E7.54, U$7.54
GP41_I2S_2_FS7: E8.54, U$8.54
GP41_I2S_2_FS8: E9.54, U$9.54
GP41_I2S_2_FS9: E10.54, U$10.54
GP41_I2S_2_FS10: E11.54, U$11.54
GP41_I2S_2_FS11: E12.54, U$12.54
GP41_I2S_2_FS12: E13.54, U$13.54
GP41_I2S_2_FS13: E14.54, U$14.54
GP41_I2S_2_FS14: E15.54, U$15.54
GP41_I2S_2_FS15: E16.54, U$16.54
GP41_I2S_2_FS16: E17.54, U$17.54
GP41_I2S_2_FS17: E18.54, U$18.54
GP41_I2S_2_FS18: E19.54, U$19.54
GP41_I2S_2_FS19: E20.54, U$20.54
GP41_I2S_2_FS20: E21.54, U$21.54
GP41_I2S_2_FS21: E22.54, U$22.54
GP41_I2S_2_FS22: E23.54, U$23.54
GP41_I2S_2_FS23: E24.54, U$24.54
GP41_I2S_2_FS24: E25.54, U$25.54
GP41_I2S_2_FS25: E26.54, U$26.54
GP41_I2S_2_FS26: E27.54, U$27.54
GP41_I2S_2_FS27: E28.54, U$28.54
GP41_I2S_2_FS28: E29.54, U$29.54
GP41_I2S_2_FS29: E30.54, U$30.54
GP41_I2S_2_FS30: E31.54, U$31.54
GP41_I2S_2_FS31: E32.54, U$32.54
GP42: E6.32, U$6.32
GP42_I2S_2_RXD: E1.50, U$3.50
GP42_I2S_2_RXD1: E2.50, U$1.50
GP42_I2S_2_RXD2: E3.50, U$2.50
GP42_I2S_2_RXD3: E4.50, U$4.50
GP42_I2S_2_RXD4: E5.50, U$5.50
GP42_I2S_2_RXD5: E6.50, U$6.50
GP42_I2S_2_RXD6: E7.50, U$7.50
GP42_I2S_2_RXD7: E8.50, U$8.50
GP42_I2S_2_RXD8: E9.50, U$9.50
GP42_I2S_2_RXD9: E10.50, U$10.50
GP42_I2S_2_RXD10: E11.50, U$11.50
GP42_I2S_2_RXD11: E12.50, U$12.50
GP42_I2S_2_RXD12: E13.50, U$13.50
GP42_I2S_2_RXD13: E14.50, U$14.50
GP42_I2S_2_RXD14: E15.50, U$15.50
GP42_I2S_2_RXD15: E16.50, U$16.50
GP42_I2S_2_RXD16: E17.50, U$17.50
GP42_I2S_2_RXD17: E18.50, U$18.50
GP42_I2S_2_RXD18: E19.50, U$19.50
GP42_I2S_2_RXD19: E20.50, U$20.50
GP42_I2S_2_RXD20: E21.50, U$21.50
GP42_I2S_2_RXD21: E22.50, U$22.50
GP42_I2S_2_RXD22: E23.50, U$23.50
GP42_I2S_2_RXD23: E24.50, U$24.50
GP42_I2S_2_RXD24: E25.50, U$25.50
GP42_I2S_2_RXD25: E26.50, U$26.50
GP42_I2S_2_RXD26: E27.50, U$27.50
GP42_I2S_2_RXD27: E28.50, U$28.50
GP42_I2S_2_RXD28: E29.50, U$29.50
GP42_I2S_2_RXD29: E30.50, U$30.50
GP42_I2S_2_RXD30: E31.50, U$31.50
GP42_I2S_2_RXD31: E32.50, U$32.50
GP43: E6.30, U$6.30
GP43_I2S_2_TXD: E1.56, U$3.56
GP43_I2S_2_TXD1: E2.56, U$1.56
GP43_I2S_2_TXD2: E3.56, U$2.56
GP43_I2S_2_TXD3: E4.56, U$4.56
GP43_I2S_2_TXD4: E5.56, U$5.56
GP43_I2S_2_TXD5: E6.56, U$6.56
GP43_I2S_2_TXD6: E7.56, U$7.56
GP43_I2S_2_TXD7: E8.56, U$8.56
GP43_I2S_2_TXD8: E9.56, U$9.56
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
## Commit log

2014-08-08 added layout for Console board. Ready for review
2014-08-08 replaced power supply with something more powerful. added fiducials
2014-08-09 added vias to usb connectors for better staking.
2014-08-12 removed stray trace
2014-08-12 removed Edzzanine from name
2014-08-25 changes to cap value
2014-08-28 Updated Readme with small description
2014-09-22 Added DCIN enable circuit replaced power button with new side shooting SMD switch Fixed dimensions corrected ground planes to not include orphans corrected name of board added DCIN pin
2014-09-22 killed .epf
2014-09-22 corrected save issue
2014-09-23 changed names of files, removed .epf
2014-09-25 file cleanup
2014-10-16 changed rev number to v01 replaced ouput capacitor on vreg to 22uF replaced filter capacitor on vreg to 47pf replaced connector footprints to add T/Brestrict to prevent solder bridging
2014-10-16 fixed bridging
2014-10-16 added ground vias to solidify ground planes. also added staking vias for USB connectors.
2014-10-16 Add a couple vias near FTDI for gnd
2014-10-17 fixed footprint
2014-10-17 removed stray Bplace from Package
2014-10-17 Ready for reds Tweaked silk positions, add some restrict between pads on QFN No known to-do items
2014-10-20 added bottom side fiducials
2014-10-20 created panel v10
2014-10-20 created giant panel
2014-10-20 corrected jumper on QFN package
2014-10-20 fixed thermal tick on panels
